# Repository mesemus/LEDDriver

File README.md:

# LEDDriver

A small project for driving 10 different leds using atmel atmega 328p (DIL) microprocessor dedicated as a PWM driver.
The driver communicates via serial interface, commands:

```
F<pin><val><pin><val>....\n
   - fade on selected pin from current value to the new one
S<pin><val><pin><val>....\n
   - set the value of the pins (without fading)
   
val is (pseudo)hexadecimal number:
  00 .. completely off
  01 - ff .. pwm on channel
  g0 .. completely on
```

This driver uses the SoftTablePWM library and is built in Eclipse, 
converting it to .ino should pose no problem.

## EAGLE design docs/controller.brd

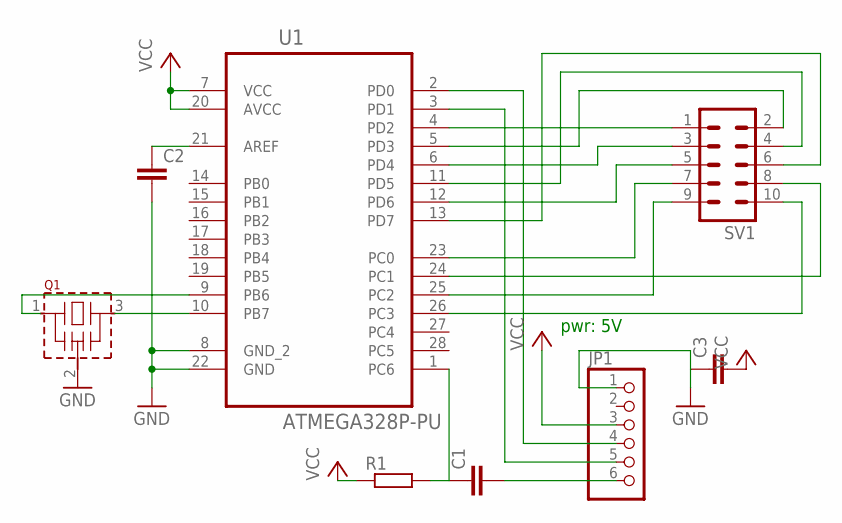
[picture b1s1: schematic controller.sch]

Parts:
C1, C2, C3: C5/3.5; C5B3.5
JP1: PINHD-1X6/90; 1X06/90
Q1: CSTLA_X; CSTLA_T
R1: R-EU_R0805; R0805
SV1: MA05-2
U1: ATMEGA328P-PU; DIP254P762X457-28

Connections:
GND: C2.2, C3.1, JP1.1, Q1.2 (VSS), U1.8 (GND_2), U1.22 (GND)
unnamed: Q1.3, U1.10 (PB7)
unnamed: Q1.1, U1.9 (PB6)
unnamed: SV1.1, U1.4 (PD2)
unnamed: SV1.2, U1.5 (PD3)
unnamed: SV1.3, U1.6 (PD4)
unnamed: SV1.4, U1.11 (PD5)
unnamed: SV1.5, U1.12 (PD6)
unnamed: SV1.6, U1.13 (PD7)
unnamed: SV1.7, U1.23 (PC0)
unnamed: SV1.8, U1.24 (PC1)
unnamed: SV1.9, U1.25 (PC2)
unnamed: SV1.10, U1.26 (PC3)
unnamed: C1.1, R1.2, U1.1 (PC6)
unnamed: C1.2, JP1.6
unnamed: JP1.4, U1.2 (PD0)
unnamed: JP1.5, U1.3 (PD1)
unnamed: C2.1, U1.21 (AREF)
VCC: C3.2, JP1.3, R1.1, U1.7 (VCC), U1.20 (AVCC)

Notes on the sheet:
pwr: 5V

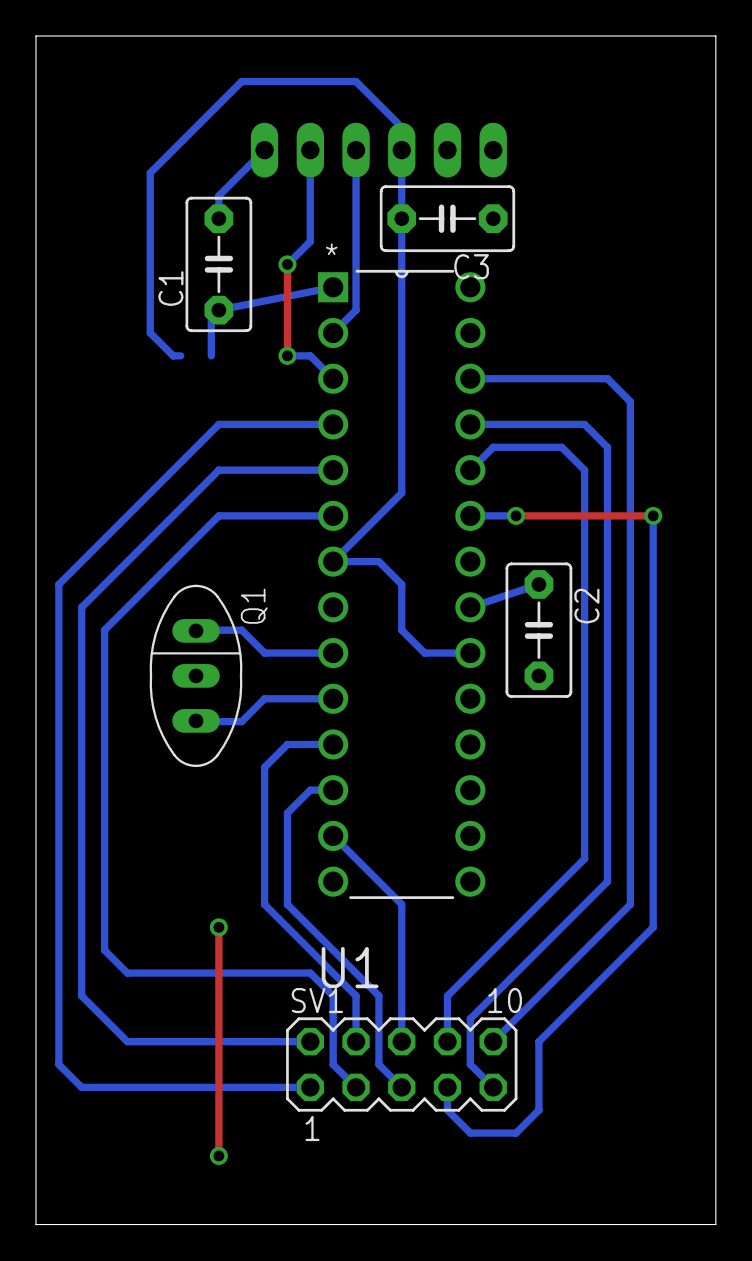
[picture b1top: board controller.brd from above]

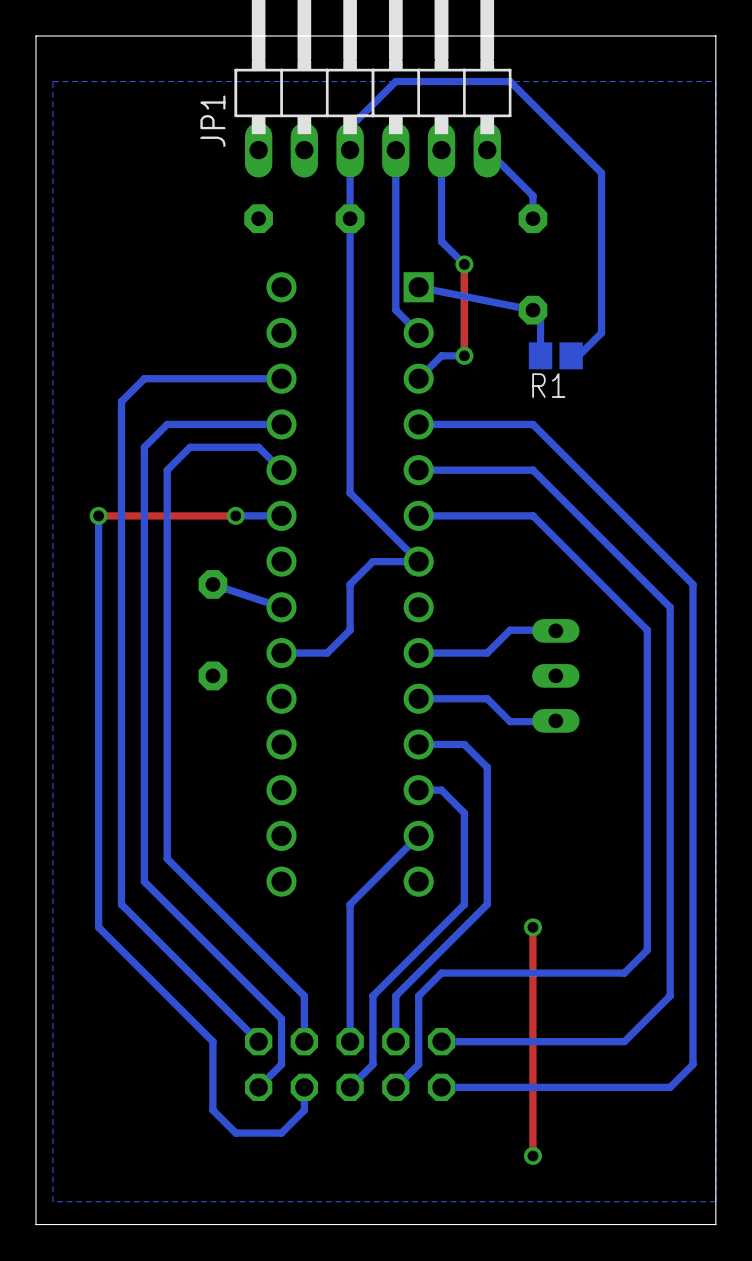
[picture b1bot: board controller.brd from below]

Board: 2 copper layers, 37.8 x 66.0 mm, 8 parts (2 on the bottom side), 19 nets.

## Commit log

2015-07-13 LEDDriver on softpwm
2015-07-13 schema etc.
2015-07-13 licence
